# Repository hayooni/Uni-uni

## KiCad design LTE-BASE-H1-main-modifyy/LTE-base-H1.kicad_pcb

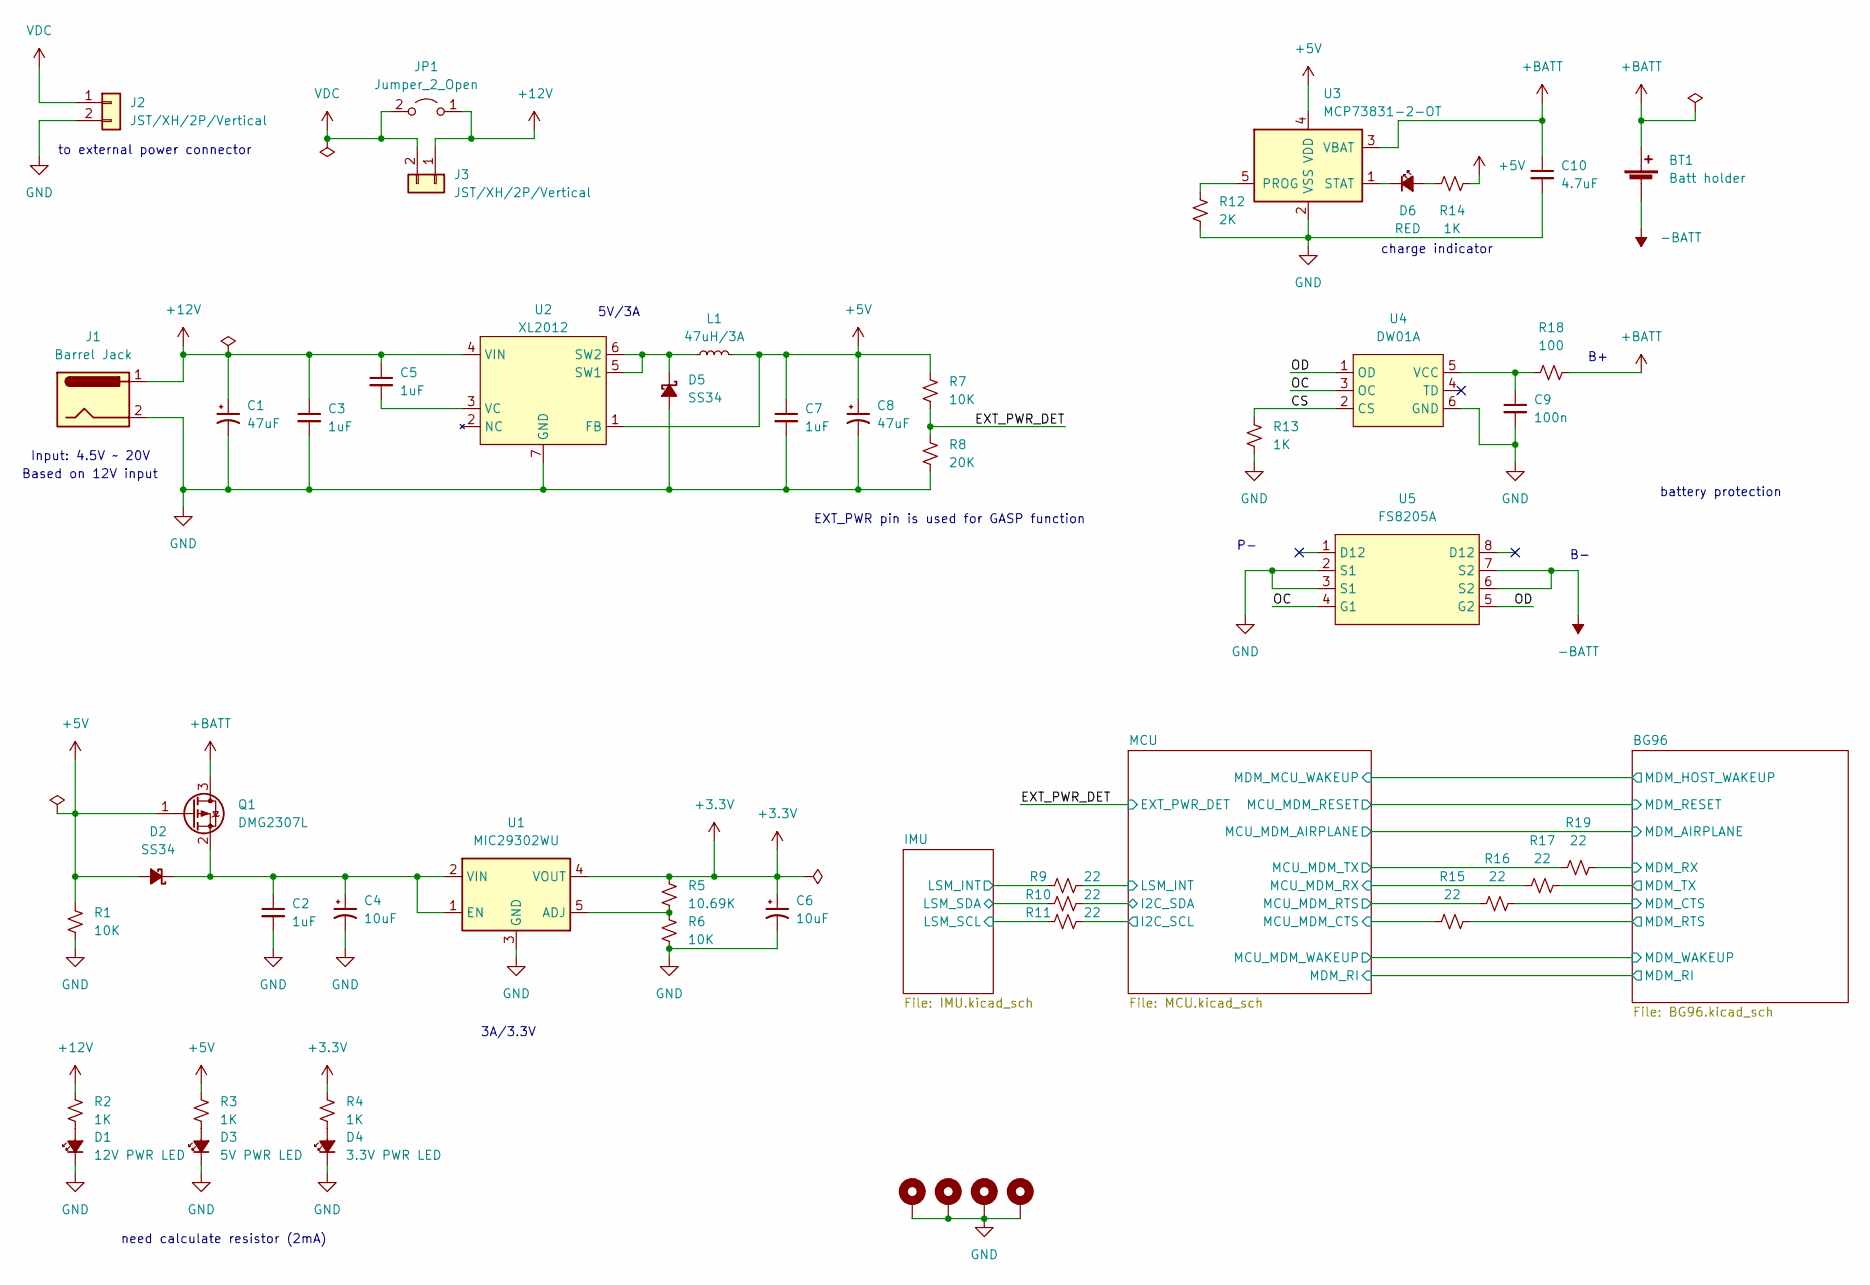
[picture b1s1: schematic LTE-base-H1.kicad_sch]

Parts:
BT1: Batt holder; BAT_1043
C1: 47uF; CP_EIA-3216-18_Kemet-A; LCSC C445227
C2, C3, C5, C7: 1uF; C_1206_3216Metric; LCSC C1848
C4, C6: 10uF; CP_EIA-3216-18_Kemet-A; LCSC C7171
C8: 47uF; CP_Elec_6.3x5.8; LCSC C445227
C9: 100n; C_0603_1608Metric; LCSC C307331
C10: 4.7uF; C_0805_2012Metric; LCSC C1848
D1: 12V PWR LED; LED_0603_1608Metric
D2, D5: SS34; D_SMA; LCSC C8678
D3: 5V PWR LED; LED_0603_1608Metric
D4: 3.3V PWR LED; LED_0603_1608Metric
D6: RED; LED_0603_1608Metric
H1, H2, H3, H4: MountingHole_Pad; MountingHole_3.2mm_M3_Pad_Via
J1: Barrel Jack; BarrelJack_Horizontal; LCSC C136744
J2, J3: JST/XH/2P/Vertical; JST_XH_B2B-XH-A_1x02_P2.50mm_Vertical
JP1: Jumper_2_Open; PinHeader_1x02_P2.54mm_Vertical
L1: 47uH/3A; L_12x12mm_H8mm; LCSC C9906
Q1: DMG2307L; SOT-23
R1, R6: 10K; R_0603_1608Metric; LCSC C25804
R2, R3, R4, R14: 1K; R_0603_1608Metric
R5: 10.69K; R_0603_1608Metric; LCSC C22857
R7: 10K; R_0603_1608Metric
R8: 20K; R_0603_1608Metric
R9, R10, R11, R15, R16, R17, R19: 22; R_0603_1608Metric; LCSC C23345
R12: 2K; R_0603_1608Metric
R13: 1K; R_0402_1005Metric; LCSC C11702
R18: 100; R_0603_1608Metric; LCSC C25076
U1: MIC29302WU; TO-263-5_TabPin3; LCSC C9013
U2: XL2012; SOP-8_3.9x4.9mm_P1.27mm; LCSC C73338
U3: MCP73831-2-OT; SOT-23-5
U4: DW01A; SOT-23-6; LCSC C14213
U5: FS8205A; TSSOP-8_4.4x3mm_P0.65mm; LCSC C16052

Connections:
+5V: C7.1, C8.1, D2.2 (A), L1.2, Q1.1 (G), R1.1, R3.2, R7.1, R14.2, U2.1 (FB), U3.4 (VDD); also elsewhere on the board
+12V: C1.1, C3.1, C5.1, J1.1, J3.1, JP1.1 (A), R2.2, U2.4 (VIN)
+BATT: BT1.1 (+), C10.1, Q1.3 (D), R18.2, U3.3 (VBAT)
-BATT: BT1.2 (-), U5.6 (S2), U5.7 (S2)
/BG96/UART_CTS: R16.2; also elsewhere on the board
/BG96/UART_RTS: R15.2; also elsewhere on the board
/BG96/UART_RX: R19.2; also elsewhere on the board
/BG96/UART_TX: R17.2; also elsewhere on the board
/CS: R13.1, U4.2 (CS)
/EXT_PWR_DET: R7.2, R8.1; also elsewhere on the board
/IMU/INT1: R9.1; also elsewhere on the board
/IMU/SCL: R11.1; also elsewhere on the board
/IMU/SDA: R10.1; also elsewhere on the board
/MCU/I2C2_SCL: R11.2; also elsewhere on the board
/MCU/I2C2_SDA: R10.2; also elsewhere on the board
/MCU/LSM_INT: R9.2; also elsewhere on the board
/MCU/USART1_CTS: R15.1; also elsewhere on the board
/MCU/USART1_RTS: R16.1; also elsewhere on the board
/MCU/USART1_RX: R17.1; also elsewhere on the board
/MCU/USART1_TX: R19.1; also elsewhere on the board
/OC: U4.3 (OC), U5.4 (G1)
/OD: U4.1 (OD), U5.5 (G2)
GND: C1.2, C2.2, C3.2, C4.2, C6.2, C7.2, C8.2, C9.2, C10.2, D1.1 (K), D3.1 (K), D4.1 (K), D5.2 (A), H1.1, H2.1, H3.1, H4.1, J1.2, J2.2, R1.2, R6.2, R8.2, R12.2, R13.2, U1.3 (GND), U2.7 (GND), U2.8 (GND), U3.2 (VSS), U4.6 (GND), U5.2 (S1), U5.3 (S1); also elsewhere on the board
unnamed: C2.1, C4.1, D2.1 (K), Q1.2 (S), U1.1 (EN), U1.2 (VIN)
unnamed: C5.2, U2.3 (VC)
unnamed: C9.1, R18.1, U4.5 (VCC)
unnamed: D1.2 (A), R2.1
unnamed: D3.2 (A), R3.1
unnamed: D4.2 (A), R4.1
unnamed: D5.1 (K), L1.1, U2.5 (SW1), U2.6 (SW2)
unnamed: D6.1 (K), U3.1 (STAT)
unnamed: D6.2 (A), R14.1
unnamed: R5.2, R6.1, U1.5 (ADJ)
unnamed: R12.1, U3.5 (PROG)
VDC: J2.1, J3.2, JP1.2 (B)

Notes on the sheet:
to external power connector
3A/3.3V
Input: 4.5V ~ 20V
EXT_PWR pin is used for GASP function
need calculate resistor (2mA)
5V/3A
charge indicator
Based on 12V input
battery protection

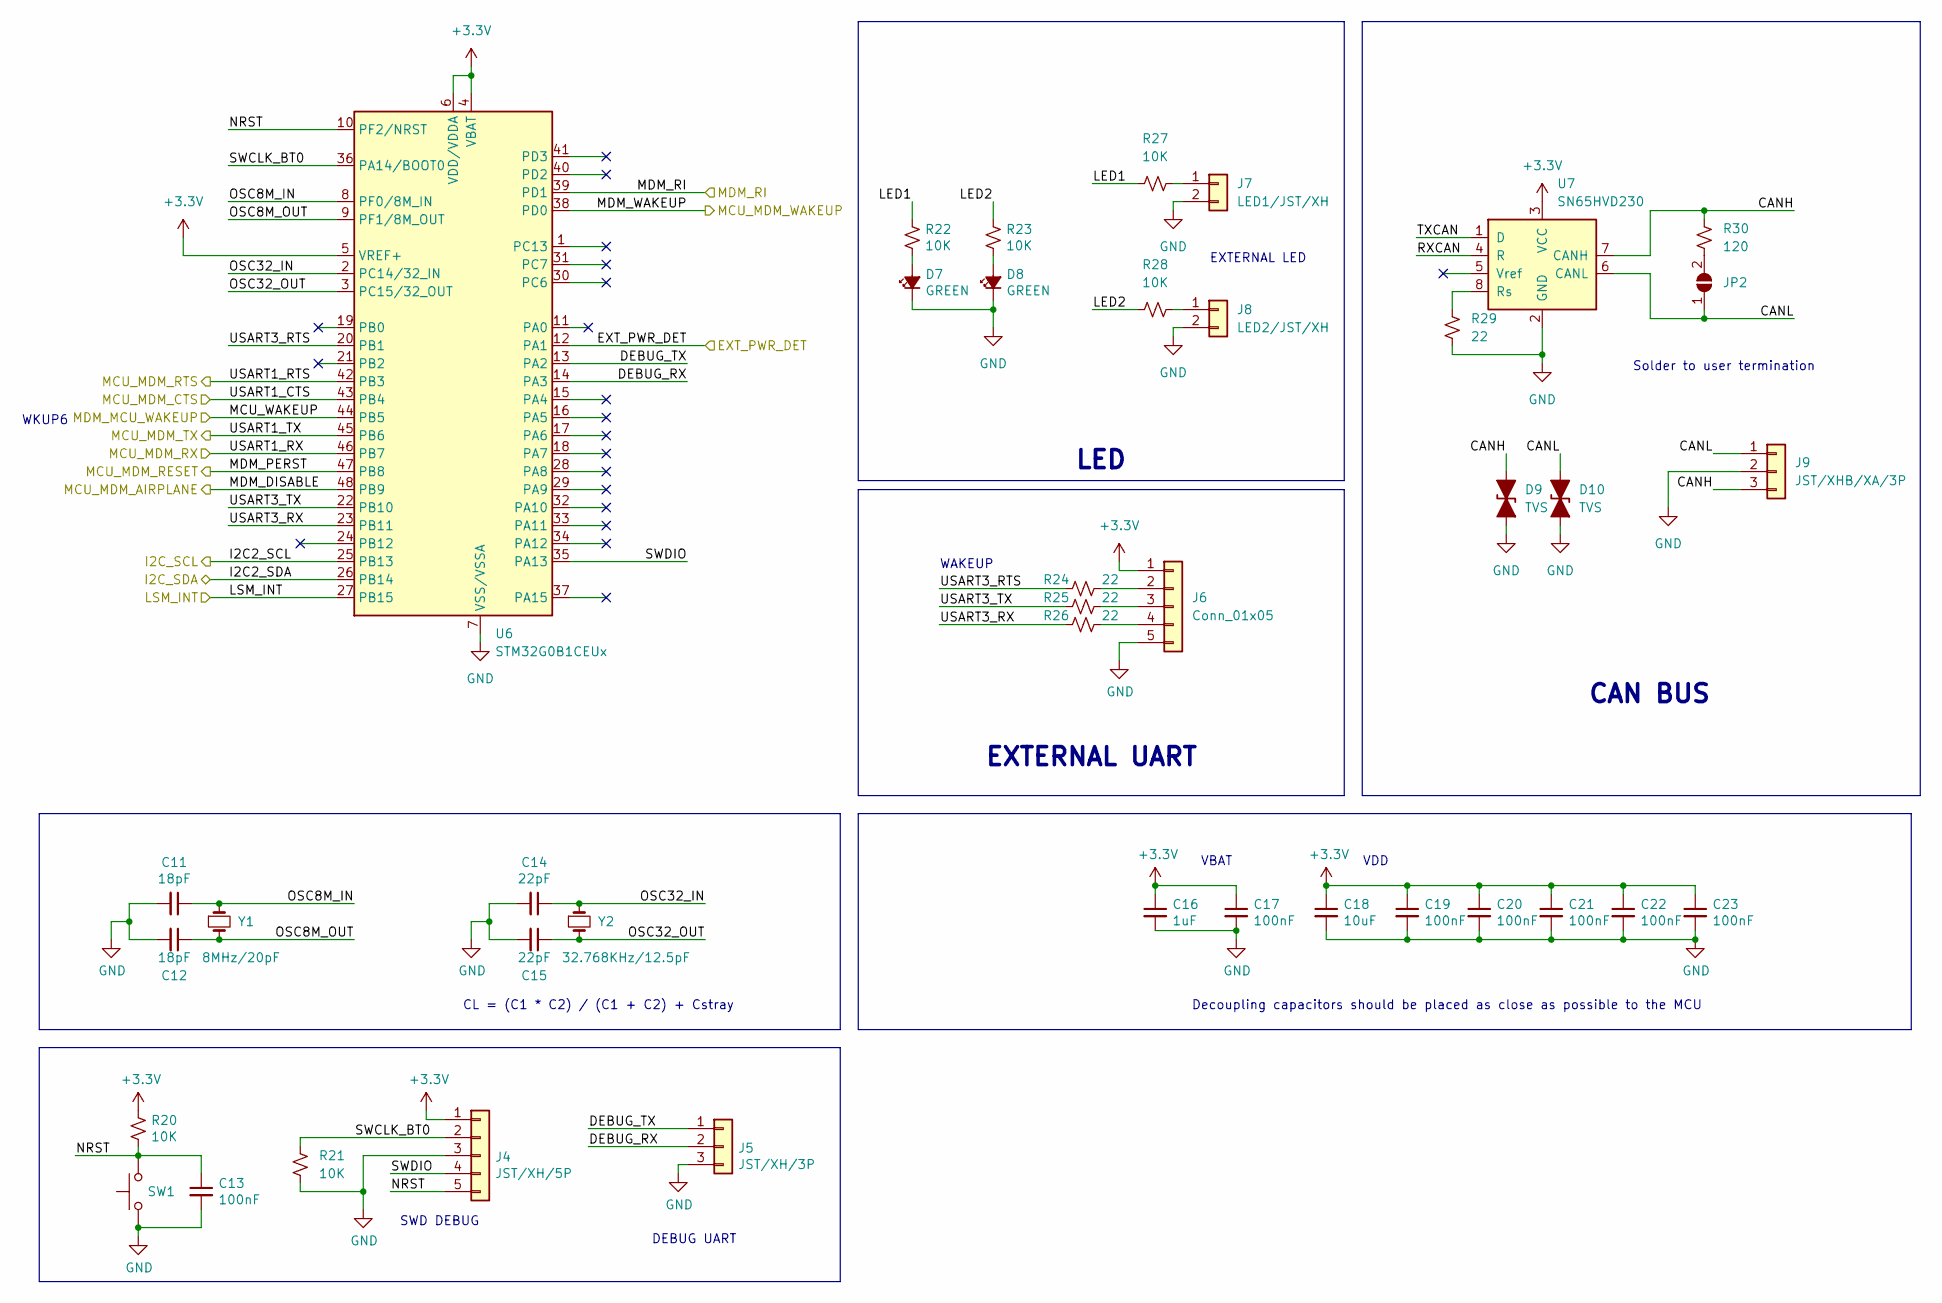
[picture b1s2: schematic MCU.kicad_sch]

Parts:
C11, C12: 18pF; C_0603_1608Metric; LCSC C1647
C13, C17, C19, C20, C21, C22, C23: 100nF; C_0603_1608Metric; LCSC C14663
C14, C15: 22pF; C_0603_1608Metric; LCSC C1653
C16: 1uF; C_0603_1608Metric; LCSC C15849
C18: 10uF; C_0603_1608Metric; LCSC C19702
D7, D8: GREEN; LED_0603_1608Metric; LCSC C72043
D9, D10: TVS; D_SOD-323; LCSC C314256
J4: JST/XH/5P; JST_XH_B5B-XH-A_1x05_P2.50mm_Vertical; LCSC C157991
J5: JST/XH/3P; JST_XH_B3B-XH-A_1x03_P2.50mm_Vertical; LCSC C144394
J6: Conn_01x05; JST_XH_B5B-XH-A_1x05_P2.50mm_Vertical
J7: LED1/JST/XH; JST_XH_B2B-XH-A_1x02_P2.50mm_Vertical
J8: LED2/JST/XH; JST_XH_B2B-XH-A_1x02_P2.50mm_Vertical
J9: JST/XHB/XA/3P; JST_XH_B3B-XH-A_1x03_P2.50mm_Vertical; LCSC C95477
JP2: SolderJumper_2_Open; SolderJumper-2_P1.3mm_Open_RoundedPad1.0x1.5mm
R20, R21, R22, R23, R27, R28: 10K; R_0603_1608Metric; LCSC C25804
R24, R25, R26, R29: 22; R_0603_1608Metric; LCSC C23345
R30: 120; R_0603_1608Metric; LCSC C22787
SW1: SW_Push; SW_SPST_PTS645; LCSC C2834943
U6: STM32G0B1CEUx; QFN-48-1EP_7x7mm_P0.5mm_EP5.6x5.6mm
U7: SN65HVD230; SOIC-8_3.9x4.9mm_P1.27mm
Y1: 8MHz/20pF; Crystal_SMD_5032-2Pin_5.0x3.2mm; LCSC C115962
Y2: 32.768KHz/12.5pF; Crystal_SMD_3215-2Pin_3.2x1.5mm; LCSC C32346

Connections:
/BG96/DTR: U6.38 (PD0); also elsewhere on the board
/BG96/RI: U6.39 (PD1); also elsewhere on the board
/BG96/nPERST: U6.47 (PB8); also elsewhere on the board
/BG96/nWAKE: U6.44 (PB5); also elsewhere on the board
/BG96/nW_DISABLE: U6.48 (PB9); also elsewhere on the board
/EXT_PWR_DET: U6.12 (PA1); also elsewhere on the board
/MCU/CANH: D9.2 (A2), J9.3, R30.1, U7.7 (CANH)
/MCU/CANL: D10.2 (A2), J9.1, JP2.1 (A), U7.6 (CANL)
/MCU/DEBUG_RX: J5.2, U6.14 (PA3)
/MCU/DEBUG_TX: J5.1, U6.13 (PA2)
/MCU/I2C2_SCL: U6.25 (PB13); also elsewhere on the board
/MCU/I2C2_SDA: U6.26 (PB14); also elsewhere on the board
/MCU/LED1: R22.1, R27.1
/MCU/LED2: R23.1, R28.1
/MCU/LSM_INT: U6.27 (PB15); also elsewhere on the board
/MCU/NRST: C13.1, J4.5, R20.2, SW1.1, U6.10 (PF2/NRST)
/MCU/OSC8M_IN: C11.1, U6.8 (PF0/8M_IN), Y1.1
/MCU/OSC8M_OUT: C12.1, U6.9 (PF1/8M_OUT), Y1.2
/MCU/OSC32_IN: C14.1, U6.2 (PC14/32_IN), Y2.1
/MCU/OSC32_OUT: C15.1, U6.3 (PC15/32_OUT), Y2.2
/MCU/RXCAN: U7.4 (R)
/MCU/SWCLK_BT0: J4.2, R21.1, U6.36 (PA14/BOOT0)
/MCU/SWDIO: J4.4, U6.35 (PA13)
/MCU/TXCAN: U7.1 (D)
/MCU/USART1_CTS: U6.43 (PB4); also elsewhere on the board
/MCU/USART1_RTS: U6.42 (PB3); also elsewhere on the board
/MCU/USART1_RX: U6.46 (PB7); also elsewhere on the board
/MCU/USART1_TX: U6.45 (PB6); also elsewhere on the board
/MCU/USART3_RTS: R24.1, U6.20 (PB1)
/MCU/USART3_RX: R26.1, U6.23 (PB11)
/MCU/USART3_TX: R25.1, U6.22 (PB10)
GND: C11.2, C12.2, C13.2, C14.2, C15.2, C16.2, C17.2, C18.2, C19.2, C20.2, C21.2, C22.2, C23.2, D7.1 (K), D8.1 (K), D9.1 (A1), D10.1 (A1), J4.3, J5.3, J6.5, J7.2, J8.2, J9.2, R21.2, R29.1, SW1.2, U6.7 (VSS/VSSA), U7.2 (GND); also elsewhere on the board
unnamed: D7.2 (A), R22.2
unnamed: D8.2 (A), R23.2
unnamed: J6.2, R24.2
unnamed: J6.3, R25.2
unnamed: J6.4, R26.2
unnamed: J7.1, R27.2
unnamed: J8.1, R28.2
unnamed: JP2.2 (B), R30.2
unnamed: R29.2, U7.8 (Rs)

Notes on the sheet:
WAKEUP
EXTERNAL UART
CL = (C1 * C2) / (C1 + C2) + Cstray
SWD DEBUG
VBAT
Decoupling capacitors should be placed as close as possible to the MCU
LED
CAN BUS
VDD
Solder to user termination
EXTERNAL LED
WKUP6
DEBUG UART

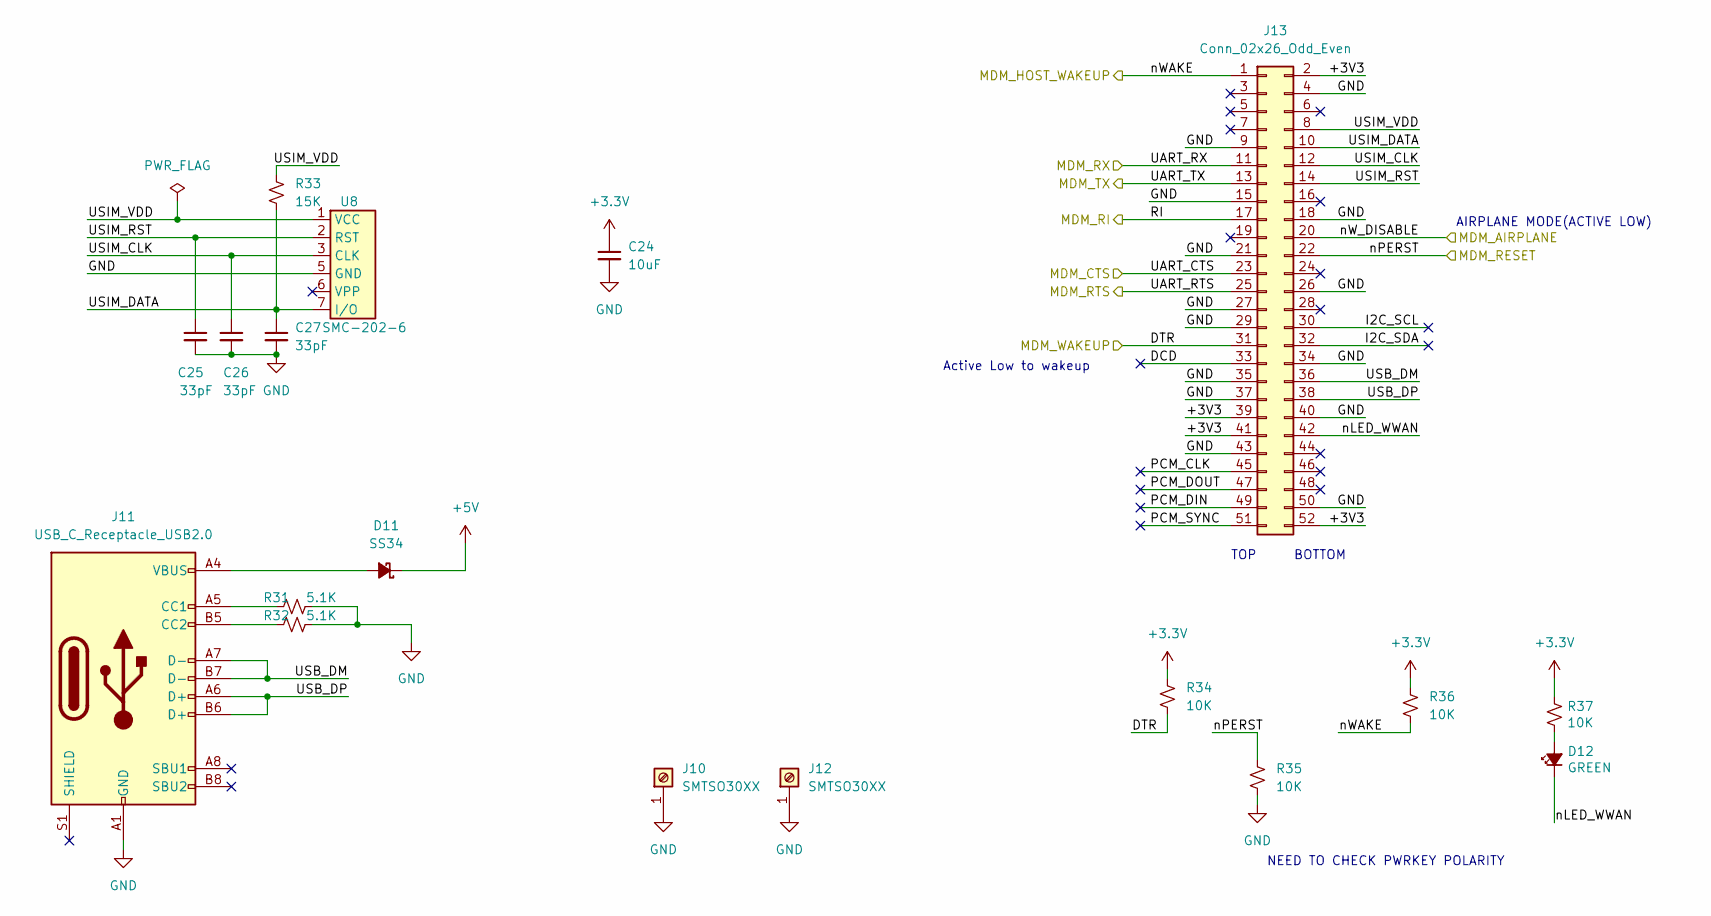
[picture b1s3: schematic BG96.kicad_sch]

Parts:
C24: 10uF; C_0603_1608Metric; LCSC C19702
C25, C26, C27: 33pF; C_0603_1608Metric_Pad1.08x0.95mm_HandSolder; LCSC C1663
D11: SS34; D_SMA; LCSC C8678
D12: GREEN; LED_0603_1608Metric; LCSC C72043
J10, J12: SMTSO30XX
J11: USB_C_Receptacle_USB2.0; USB_C_Receptacle_HRO_TYPE-C-31-M-12; LCSC C165948
J13: Conn_02x26_Odd_Even; BUS_PCI_Express_Mini_Full; LCSC C444928
R31, R32: 5.1K; R_0805_2012Metric; LCSC C27834
R33: 15K; R_0603_1608Metric_Pad0.98x0.95mm_HandSolder; LCSC C22809
R34, R35, R36: 10K; R_0603_1608Metric_Pad0.98x0.95mm_HandSolder; LCSC C25804
R37: 10K; R_0603_1608Metric; LCSC C25804
U8: SMC-202-6; LCSC C266634

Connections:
+5V: D11.1 (K); also elsewhere on the board
/BG96/DCD: J13.33
/BG96/DTR: J13.31, R34.2; also elsewhere on the board
/BG96/I2C_SCL: J13.30
/BG96/I2C_SDA: J13.32
/BG96/PCM_CLK: J13.45
/BG96/PCM_DIN: J13.49
/BG96/PCM_DOUT: J13.47
/BG96/PCM_SYNC: J13.51
/BG96/RI: J13.17; also elsewhere on the board
/BG96/UART_CTS: J13.23; also elsewhere on the board
/BG96/UART_RTS: J13.25; also elsewhere on the board
/BG96/UART_RX: J13.11; also elsewhere on the board
/BG96/UART_TX: J13.13; also elsewhere on the board
/BG96/USB_DM: J11.A7 (D-), J11.B7 (D-), J13.36
/BG96/USB_DP: J11.A6 (D+), J11.B6 (D+), J13.38
/BG96/USIM_CLK: C26.1, J13.12, U8.3 (CLK)
/BG96/USIM_DATA: C27.1, J13.10, R33.2, U8.7 (I/O)
/BG96/USIM_RST: C25.1, J13.14, U8.2 (RST)
/BG96/USIM_VDD: J13.8, R33.1, U8.1 (VCC)
/BG96/nLED_WWAN: D12.1 (K), J13.42
/BG96/nPERST: J13.22, R35.1; also elsewhere on the board
/BG96/nWAKE: J13.1, R36.2; also elsewhere on the board
/BG96/nW_DISABLE: J13.20; also elsewhere on the board
GND: C24.2, C25.2, C26.2, C27.2, J10.1, J11.A1 (GND), J11.A12 (GND), J11.B1 (GND), J11.B12 (GND), J12.1, J13.4, J13.9, J13.15, J13.18, J13.21, J13.26, J13.27, J13.29, J13.34, J13.35, J13.37, J13.40, J13.43, J13.50, R31.1, R32.1, R35.2, U8.5 (GND); also elsewhere on the board
unnamed: D11.2 (A), J11.A4 (VBUS), J11.A9 (VBUS), J11.B4 (VBUS), J11.B9 (VBUS)
unnamed: D12.2 (A), R37.2
unnamed: J11.A5 (CC1), R31.2
unnamed: J11.B5 (CC2), R32.2

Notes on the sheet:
BOTTOM
AIRPLANE MODE(ACTIVE LOW)
Active Low to wakeup
TOP
NEED TO CHECK PWRKEY POLARITY

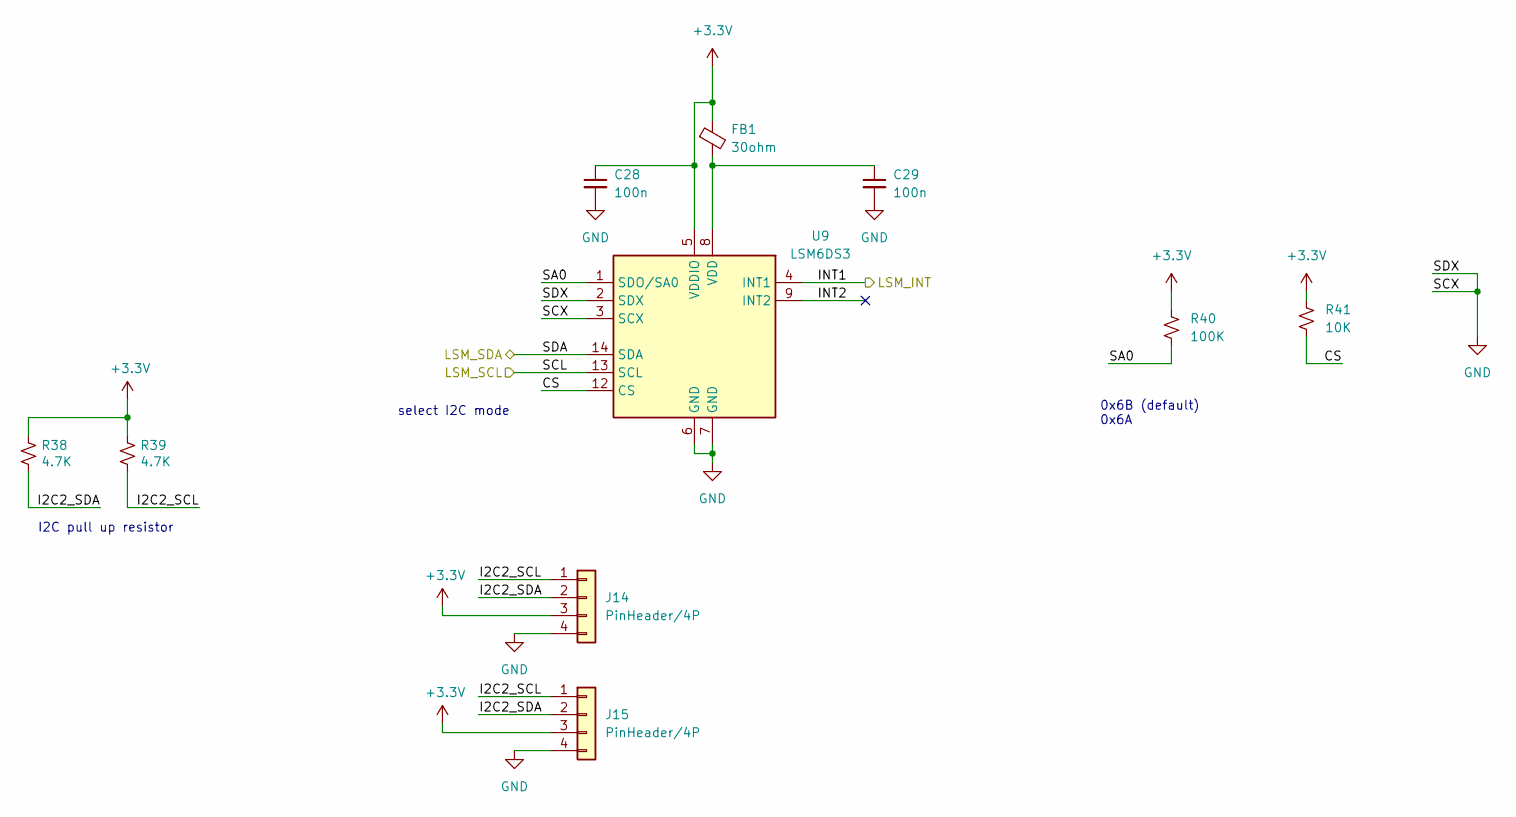
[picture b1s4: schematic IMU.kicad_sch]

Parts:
C28, C29: 100n; C_0805_2012Metric
FB1: 30ohm; R_0805_2012Metric
J14, J15: PinHeader/4P; PinSocket_1x04_P2.54mm_Vertical
R38, R39: 4.7K; R_0603_1608Metric
R40: 100K; R_0805_2012Metric
R41: 10K; R_0805_2012Metric
U9: LSM6DS3; LGA-14_3x2.5mm_P0.5mm_LayoutBorder3x4y

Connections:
/IMU/CS: R41.2, U9.12 (CS)
/IMU/I2C2_SCL: J14.1, J15.1, R39.2
/IMU/I2C2_SDA: J14.2, J15.2, R38.2
/IMU/INT1: U9.4 (INT1); also elsewhere on the board
/IMU/INT2: U9.9 (INT2)
/IMU/SA0: R40.2, U9.1 (SDO/SA0)
/IMU/SCL: U9.13 (SCL); also elsewhere on the board
/IMU/SDA: U9.14 (SDA); also elsewhere on the board
GND: C28.2, C29.2, J14.4, J15.4, U9.2 (SDX), U9.3 (SCX), U9.6 (GND), U9.7 (GND); also elsewhere on the board
unnamed: C29.1, FB1.2, U9.8 (VDD)

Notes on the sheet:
select I2C mode
0x6B (default) 0x6A
I2C pull up resistor

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
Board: 4 copper layers, 125 parts (0 on the bottom side), 82 nets, no tracks yet.

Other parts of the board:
kibuzzard-61FFCA2F: G***; kibuzzard-61FFCA2F
kibuzzard-61FFCAE2: G***; kibuzzard-61FFCAE2
kibuzzard-61FFCAF5: G***; kibuzzard-61FFCAF5
kibuzzard-61FFCBAB: G***; kibuzzard-61FFCBAB
kibuzzard-61FFCBC3: G***; kibuzzard-61FFCBC3
kibuzzard-6200D0E6: G***; kibuzzard-6200D0E6

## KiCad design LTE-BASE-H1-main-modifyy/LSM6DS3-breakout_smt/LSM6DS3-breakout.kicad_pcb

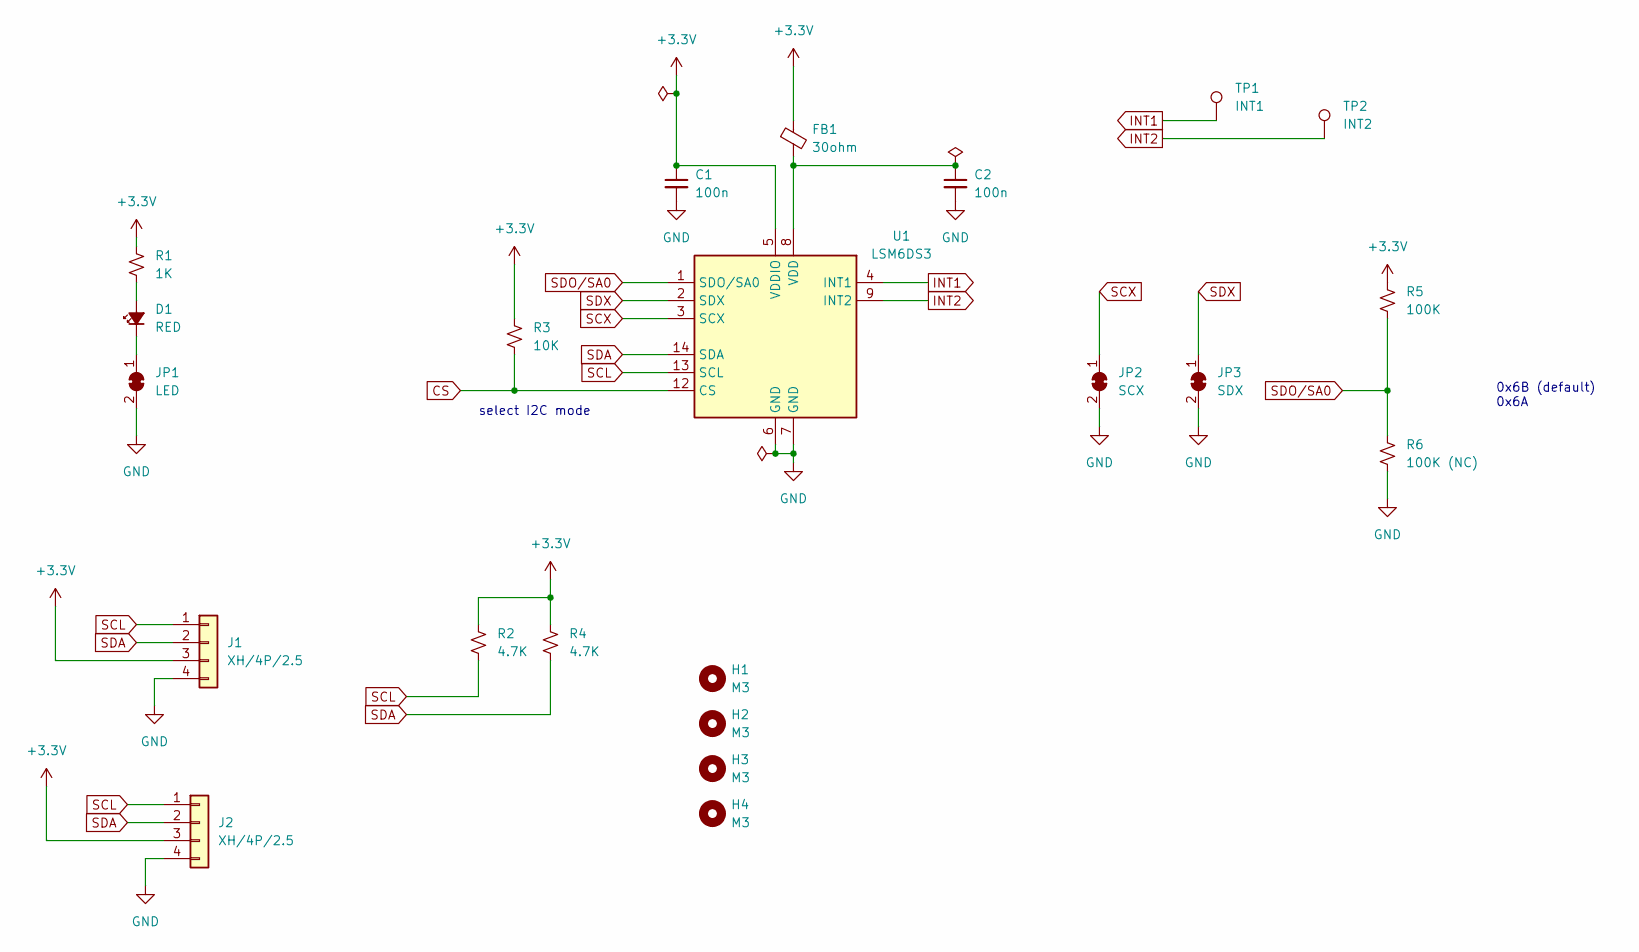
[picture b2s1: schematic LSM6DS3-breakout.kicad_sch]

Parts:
C1, C2: 100n; C_0805_2012Metric
D1: RED; LED_0805_2012Metric
FB1: 30ohm; R_0805_2012Metric
H1, H2, H3, H4: M3; MountingHole_3.2mm_M3_Pad_Via
J1, J2: XH/4P/2.5; JST_XH_B4B-XH-A_1x04_P2.50mm_Vertical
JP1: LED; SolderJumper-2_P1.3mm_Bridged_RoundedPad1.0x1.5mm
JP2: SCX; SolderJumper-2_P1.3mm_Bridged_RoundedPad1.0x1.5mm
JP3: SDX; SolderJumper-2_P1.3mm_Bridged_RoundedPad1.0x1.5mm
R1: 1K; R_0805_2012Metric
R2, R4: 4.7K; R_0805_2012Metric
R3: 10K; R_0805_2012Metric
R5: 100K; R_0805_2012Metric
R6: 100K (NC); R_0805_2012Metric
TP1: INT1; TestPoint_Keystone_5000-5004_Miniature
TP2: INT2; TestPoint_Keystone_5000-5004_Miniature
U1: LSM6DS3; LGA-14_3x2.5mm_P0.5mm_LayoutBorder3x4y

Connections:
+3.3V: C1.1, FB1.1, J1.3, J2.3, R1.1, R2.1, R3.1, R4.1, R5.1, U1.5 (VDDIO)
CS: R3.2, U1.12 (CS)
GND: C1.2, C2.2, J1.4, J2.4, JP1.2 (B), JP2.2 (B), JP3.2 (B), R6.2, U1.6 (GND), U1.7 (GND)
INT1: TP1.1, U1.4 (INT1)
INT2: TP2.1, U1.9 (INT2)
unnamed: C2.1, FB1.2, U1.8 (VDD)
unnamed: D1.1 (K), JP1.1 (A)
unnamed: D1.2 (A), R1.2
SCL: J1.1, J2.1, R2.2, U1.13 (SCL)
SCX: JP2.1 (A), U1.3 (SCX)
SDA: J1.2, J2.2, R4.2, U1.14 (SDA)
SDO/SA0: R5.2, R6.1, U1.1 (SDO/SA0)
SDX: JP3.1 (A), U1.2 (SDX)

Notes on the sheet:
0x6B (default) 0x6A
select I2C mode

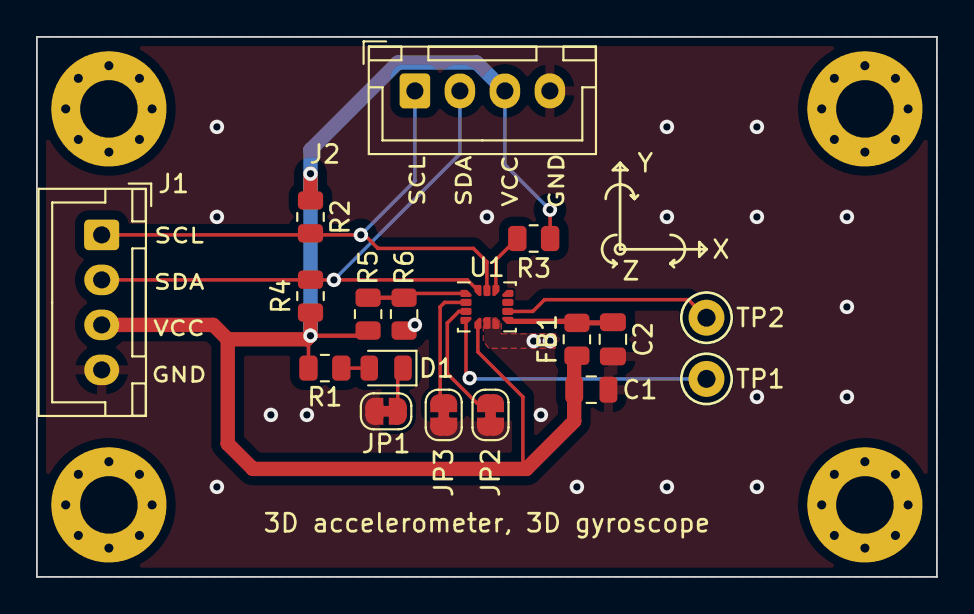
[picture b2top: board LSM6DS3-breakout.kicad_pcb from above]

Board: 2 copper layers, 50.0 x 30.0 mm, 22 parts (0 on the bottom side), 13 nets.

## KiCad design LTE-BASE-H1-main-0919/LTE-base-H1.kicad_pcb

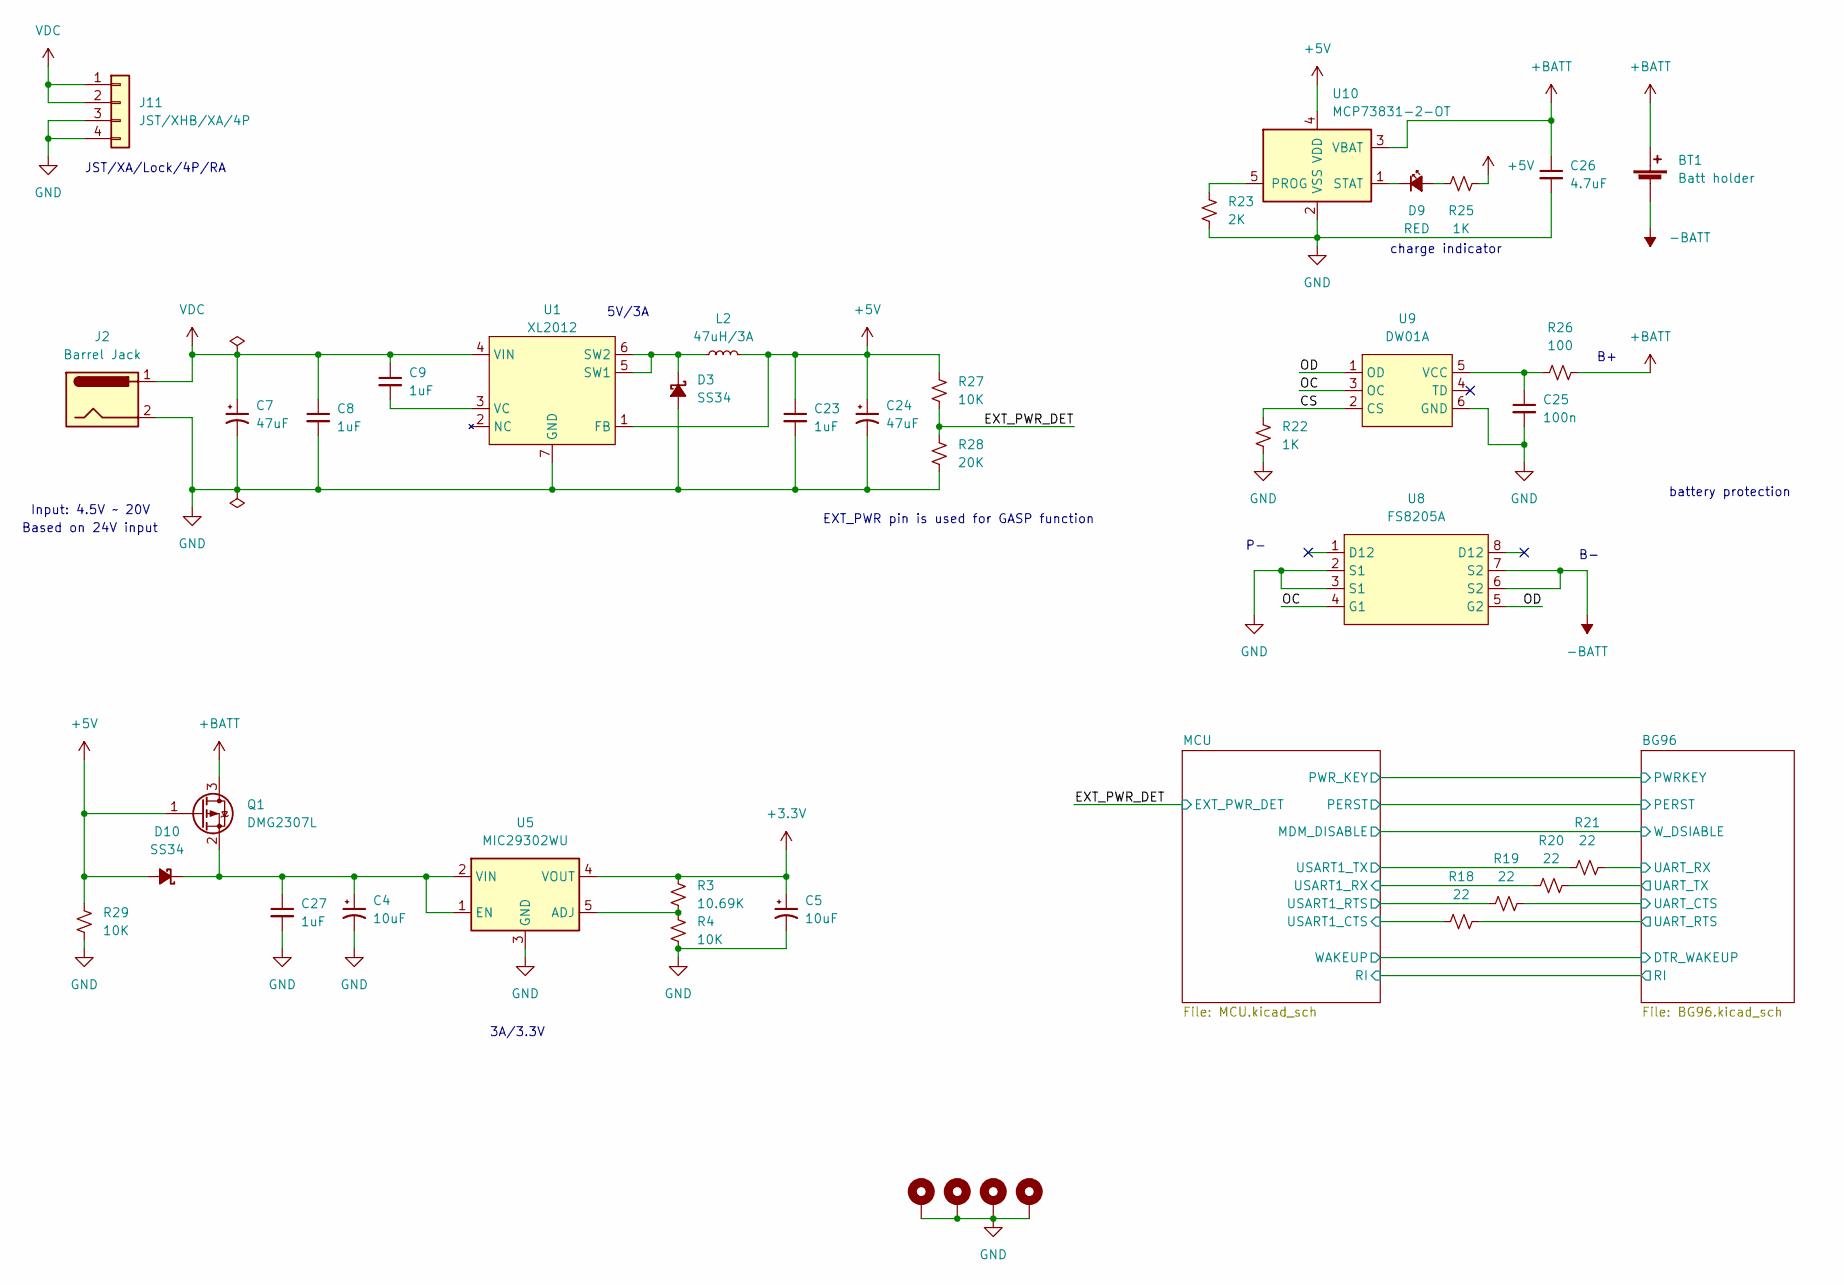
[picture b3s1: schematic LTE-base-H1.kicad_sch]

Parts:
BT1: Batt holder; BAT_1043
C4, C5: 10uF; CP_EIA-3216-18_Kemet-A; LCSC C7171
C7, C24: 47uF; CP_Elec_6.3x5.8; LCSC C445227
C8, C9, C23, C27: 1uF; C_1206_3216Metric; LCSC C1848
C25: 100n; C_0603_1608Metric; LCSC C307331
C26: 4.7uF; C_0805_2012Metric; LCSC C1848
D3, D10: SS34; D_SMA; LCSC C8678
D9: RED; LED_0603_1608Metric
H1, H2, H3, H4: MountingHole_Pad; MountingHole_3.2mm_M3_Pad_Via
J2: Barrel Jack; BarrelJack_Horizontal; LCSC C136744
J11: JST/XHB/XA/4P; JST_XA_B04B-XASK-1_1x04_P2.50mm_Vertical; LCSC C95476
L2: 47uH/3A; L_12x12mm_H8mm; LCSC C9906
Q1: DMG2307L; SOT-23
R3: 10.69K; R_0603_1608Metric; LCSC C22857
R4, R29: 10K; R_0603_1608Metric; LCSC C25804
R18, R19, R20, R21: 22; R_0603_1608Metric; LCSC C23345
R22: 1K; R_0402_1005Metric; LCSC C11702
R23: 2K; R_0603_1608Metric
R25: 1K; R_0603_1608Metric
R26: 100; R_0603_1608Metric; LCSC C25076
R27: 10K; R_0603_1608Metric
R28: 20K; R_0603_1608Metric
U1: XL2012; SOP-8_3.9x4.9mm_P1.27mm; LCSC C73338
U5: MIC29302WU; TO-263-5_TabPin3; LCSC C9013
U8: FS8205A; TSSOP-8_4.4x3mm_P0.65mm; LCSC C16052
U9: DW01A; SOT-23-6; LCSC C14213
U10: MCP73831-2-OT; SOT-23-5

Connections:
+5V: C23.1, C24.1, D10.2 (A), L2.2, Q1.1 (G), R25.2, R27.1, R29.1, U1.1 (FB), U10.4 (VDD); also elsewhere on the board
+BATT: BT1.1 (+), C26.1, Q1.3 (D), R26.2, U10.3 (VBAT)
-BATT: BT1.2 (-), U8.6 (S2), U8.7 (S2)
/BG96/UART_CTS: R19.2; also elsewhere on the board
/BG96/UART_RTS: R18.2; also elsewhere on the board
/BG96/UART_RX: R21.2; also elsewhere on the board
/BG96/UART_TX: R20.2; also elsewhere on the board
/CS: R22.1, U9.2 (CS)
/EXT_PWR_DET: R27.2, R28.1; also elsewhere on the board
/MCU/USART1_CTS: R18.1; also elsewhere on the board
/MCU/USART1_RTS: R19.1; also elsewhere on the board
/MCU/USART1_RX: R20.1; also elsewhere on the board
/MCU/USART1_TX: R21.1; also elsewhere on the board
/OC: U8.4 (G1), U9.3 (OC)
/OD: U8.5 (G2), U9.1 (OD)
GND: C4.2, C5.2, C7.2, C8.2, C23.2, C24.2, C25.2, C26.2, C27.2, D3.2 (A), H1.1, H2.1, H3.1, H4.1, J2.2, J11.3, J11.4, R4.2, R22.2, R23.2, R28.2, R29.2, U1.7 (GND), U1.8 (GND), U5.3 (GND), U8.2 (S1), U8.3 (S1), U9.6 (GND), U10.2 (VSS); also elsewhere on the board
unnamed: C9.2, U1.3 (VC)
unnamed: C25.1, R26.1, U9.5 (VCC)
unnamed: C4.1, C27.1, D10.1 (K), Q1.2 (S), U5.1 (EN), U5.2 (VIN)
unnamed: D3.1 (K), L2.1, U1.5 (SW1), U1.6 (SW2)
unnamed: D9.1 (K), U10.1 (STAT)
unnamed: D9.2 (A), R25.1
unnamed: R3.2, R4.1, U5.5 (ADJ)
unnamed: R23.1, U10.5 (PROG)
VDC: C7.1, C8.1, C9.1, J2.1, J11.1, J11.2, U1.4 (VIN)

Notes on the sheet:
JST/XA/Lock/4P/RA
3A/3.3V
Input: 4.5V ~ 20V
EXT_PWR pin is used for GASP function
5V/3A
charge indicator
Based on 24V input
battery protection
